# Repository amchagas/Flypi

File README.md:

#### Flypi - An open source, modular, affordable tool for imaging experiments.

Hi! Thanks for dropping by. This project started during one of the summer courses organized by [Trend in Africa](www.trendinafrica.org). It developed to the current state due to the efforts of many people along the way. In special Tom Baden, Lucia Prieto, and Edwin Cruz. A paper describing the system was published in [Plos Biology](http://journals.plos.org/plosbiology/article?id=10.1371/journal.pbio.2002702).

 Version 1.0 was released with the paper and can be found [here](https://github.com/amchagas/Flypi/tree/v1.0.0).

The system can be used for optical microscopy, fluorescence, behavioural tracking, optogenetics, calcium imaging and thermogenetics (see examples recorded with the system below).

#### Some samples imaged with the device:

|     |   |    |
|---|---|---|
|    |   |    |

### Custom PCB

You can order the PCBs and buy the parts to assemble them through the [Kitspace page](https://kitspace.org/boards/github.com/prometheus-science/FlyPi).

#### Necessary Libraries:

LED Ring from Adafruit:
https://github.com/adafruit/Adafruit_NeoPixel

LED Matrix from Adafruit:
https://github.com/adafruit/Adafruit-LED-Backpack-Library

gpac library:
sudo apt-get update
sudo apt-get install gpac

## *.h264 conversion to *.avi:
Done via gpac. MP4BOX.

## Zipped SD Card image containing Raspian image with all things installed:

[IMAGE](https://bit.ly/flyipimg)

## Contributors ✨

Thanks goes to these wonderful people ([emoji key](https://allcontributors.org/docs/en/emoji-key)):

<!-- ALL-CONTRIBUTORS-LIST:START - Do not remove or modify this section -->
<!-- prettier-ignore -->
<table>
  <tr>
    <td align="center"><a href="http://www.openeuroscience.com"><br /><sub><b>Andre Maia Chagas</b></sub></a><br /><a href="https://github.com/amchagas/Flypi/commits?author=amchagas" title="Code">💻</a> <a href="#design-amchagas" title="Design">🎨</a> <a href="https://github.com/amchagas/Flypi/commits?author=amchagas" title="Documentation">📖</a></td><td align="center"><a href="https://github.com/icaven"><br /><sub><b>icaven</b></sub></a><br /><a href="#design-icaven" title="Design">🎨</a></td>
    <td align="center"><a href="https://github.com/GrandeCappuccino"><br /><sub><b>Edwin Cruz</b></sub></a><br /><a href="#design-GrandeCappuccino" title="Design">🎨</a></td><td align="center"><a href="http://www.badenlab.org"><br /><sub><b>Tom Baden</b></sub></a><br /><a href="#design-TomBaden" title="Design">🎨</a> <a href="https://github.com/amchagas/Flypi/commits?author=TomBaden" title="Code">💻</a></td><td align="center"><a href="https://github.com/isobianin"><br /><sub><b>Ihor Sobianin</b></sub></a><br /><a href="#design-isobianin" title="Design">🎨</a></td>
    <td align="center"><a href="https://kitspace.org"><br /><sub><b>Kaspar Emanuel</b></sub></a><br /><a href="https://github.com/amchagas/Flypi/commits?author=kasbah" title="Code">💻</a></td><td align="center"><a href="https://github.com/ifriad"><br /><sub><b>ifriad</b></sub></a><br /><a href="#design-ifriad" title="Design">🎨</a> <a href="https://github.com/amchagas/Flypi/commits?author=ifriad" title="Code">💻</a></td>
  </tr>
</table>

<!-- ALL-CONTRIBUTORS-LIST:END -->

This project follows the [all-contributors](https://github.com/all-contributors/all-contributors) specification. Contributions of any kind welcome!

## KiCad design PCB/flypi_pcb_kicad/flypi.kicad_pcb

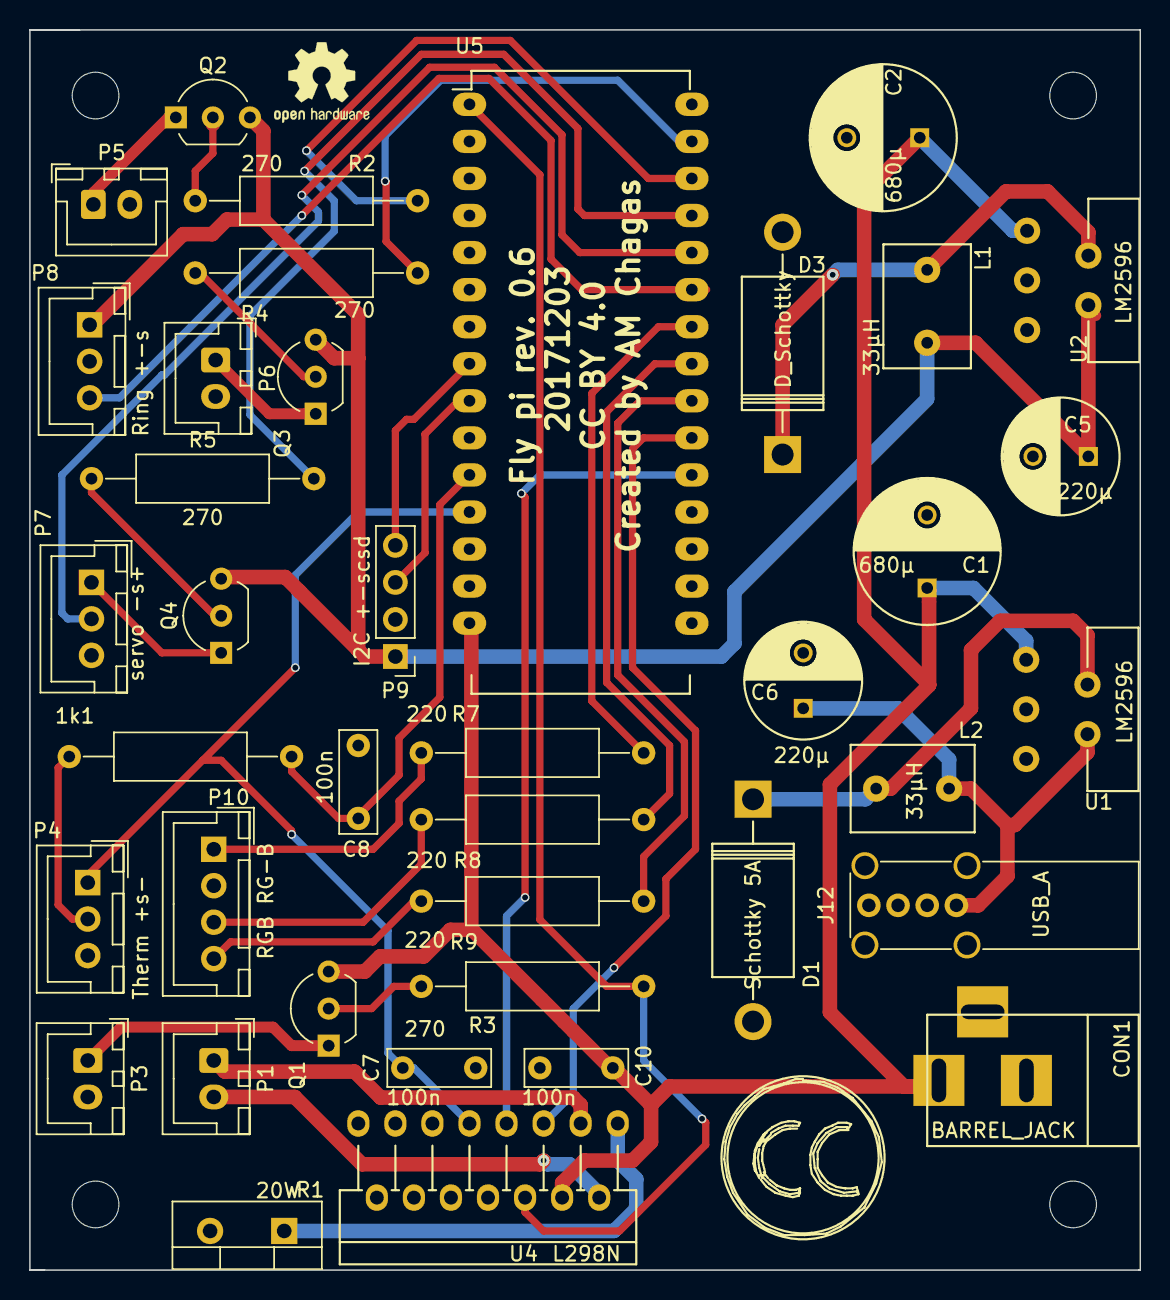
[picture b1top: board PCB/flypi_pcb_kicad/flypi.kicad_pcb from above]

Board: 2 copper layers, 76.1 x 85.0 mm, 40 parts (0 on the bottom side), 36 nets.

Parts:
1k1: R; R_Axial_DIN0309_L9.0mm_D3.2mm_P15.24mm_Horizontal
 : MountingHole_3.2mm_M3_DIN965
C1, C2: 680µ; C_Radial_D10_L21_P5
C5, C6: 220µ; C_Radial_D8_L13_P3.8
C7, C8, C10: 100n; C_Rect_L7.0mm_W2.5mm_P5.00mm
CON1: BARREL_JACK
D1: Schottky 5A; Diode_DO-201AD_Horizontal_RM15
D3: D_Schottky; Diode_DO-201AD_Horizontal_RM15
J12: USB_A; USB_A_Vertical
L1, L2: 33µH; Neosid_Inductor_MA-Bs75
P1: PeltS1S2; JST_XH_B2B-XH-A_1x02_P2.50mm_Vertical
P3: Fan+-; JST_XH_B2B-XH-A_1x02_P2.50mm_Vertical
P4: Therm +s-; JST_XH_B03B-XH-A_03x2.50mm_Straight
P5: HP1+-; JST_XH_B2B-XH-A_1x02_P2.50mm_Vertical
P6: HP2+-; JST_XH_B2B-XH-A_1x02_P2.50mm_Vertical
P7: servo -s+; JST_XH_B03B-XH-A_03x2.50mm_Straight
P8: Ring +-s; JST_XH_B03B-XH-A_03x2.50mm_Straight
P9: I2C +-scsd; Socket_Strip_Straight_1x04_Pitch2.54mm
P10: RGB RG-B; JST_XH_B04B-XH-A_04x2.50mm_Straight
Q1, Q3, Q4: 1A_NPN_EBC; TO-92_Inline_Wide
Q2: 1A-NPN-EBC; TO-92_Inline_Wide
R1: 20W; TO-220-2_Vertical
R2, R3, R4, R5: 270; R_Axial_DIN0309_L9.0mm_D3.2mm_P15.24mm_Horizontal
R7, R8, R9: 220; R_Axial_DIN0309_L9.0mm_D3.2mm_P15.24mm_Horizontal
U1, U2: LM2596
U4: L298N; Multiwatt_15_Vertical
U5: arduino_mini; DIP-30_W15.24mm_LongPads

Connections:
GND: C1.2, C2.2, C5.2, C6.2, C7.2, C8.1, C10.1, CON1.2, CON1.3, D1.2, D3.2, J12.4, J12.5, P3.2, P4.3, P5.2, P6.2, P7.3, P8.2, P9.2, P10.2, R1.2, U1.3, U1.5, U2.3, U2.5, U4.8, U5.14, U5.19
unnamed: 1k1.1, C8.2, U5.11
unnamed: 1k1.2, P4.2
unnamed: C1.1, C2.1, C10.2, CON1.1, Q1.3, U1.1, U2.1, U4.4, U5.15
unnamed: C5.1, L1.2, P8.1, P9.1, Q2.3, Q3.3, Q4.3, U2.4
unnamed: C6.1, J12.1, L2.2, U1.4
unnamed: C7.1, P4.1, U4.9, U5.12
unnamed: D1.1, L2.1, U1.2
unnamed: D3.1, L1.1, U2.2
unnamed: P1.1, U4.3
unnamed: P1.2, U4.2
unnamed: P3.1, Q1.1
unnamed: P5.1, Q2.1
unnamed: P6.1, Q3.1
unnamed: P7.1, Q4.1
unnamed: P7.2, U5.26
unnamed: P8.3, U5.25
unnamed: P9.3, U5.9
unnamed: P9.4, U5.8
unnamed: P10.1, R7.1
unnamed: P10.3, R8.1
unnamed: P10.4, R9.1
unnamed: Q1.2, R3.1
unnamed: Q2.2, R2.1
unnamed: Q3.2, R4.1
unnamed: Q4.2, R5.1
unnamed: R1.1, U4.1
unnamed: R2.2, U5.28
unnamed: R3.2, U4.6, U5.1
unnamed: R4.2, U5.29
unnamed: R5.2, U5.27
unnamed: R7.2, U5.24
unnamed: R8.2, U5.23
unnamed: R9.2, U5.22
unnamed: U4.5, U5.21
unnamed: U4.7, U5.20

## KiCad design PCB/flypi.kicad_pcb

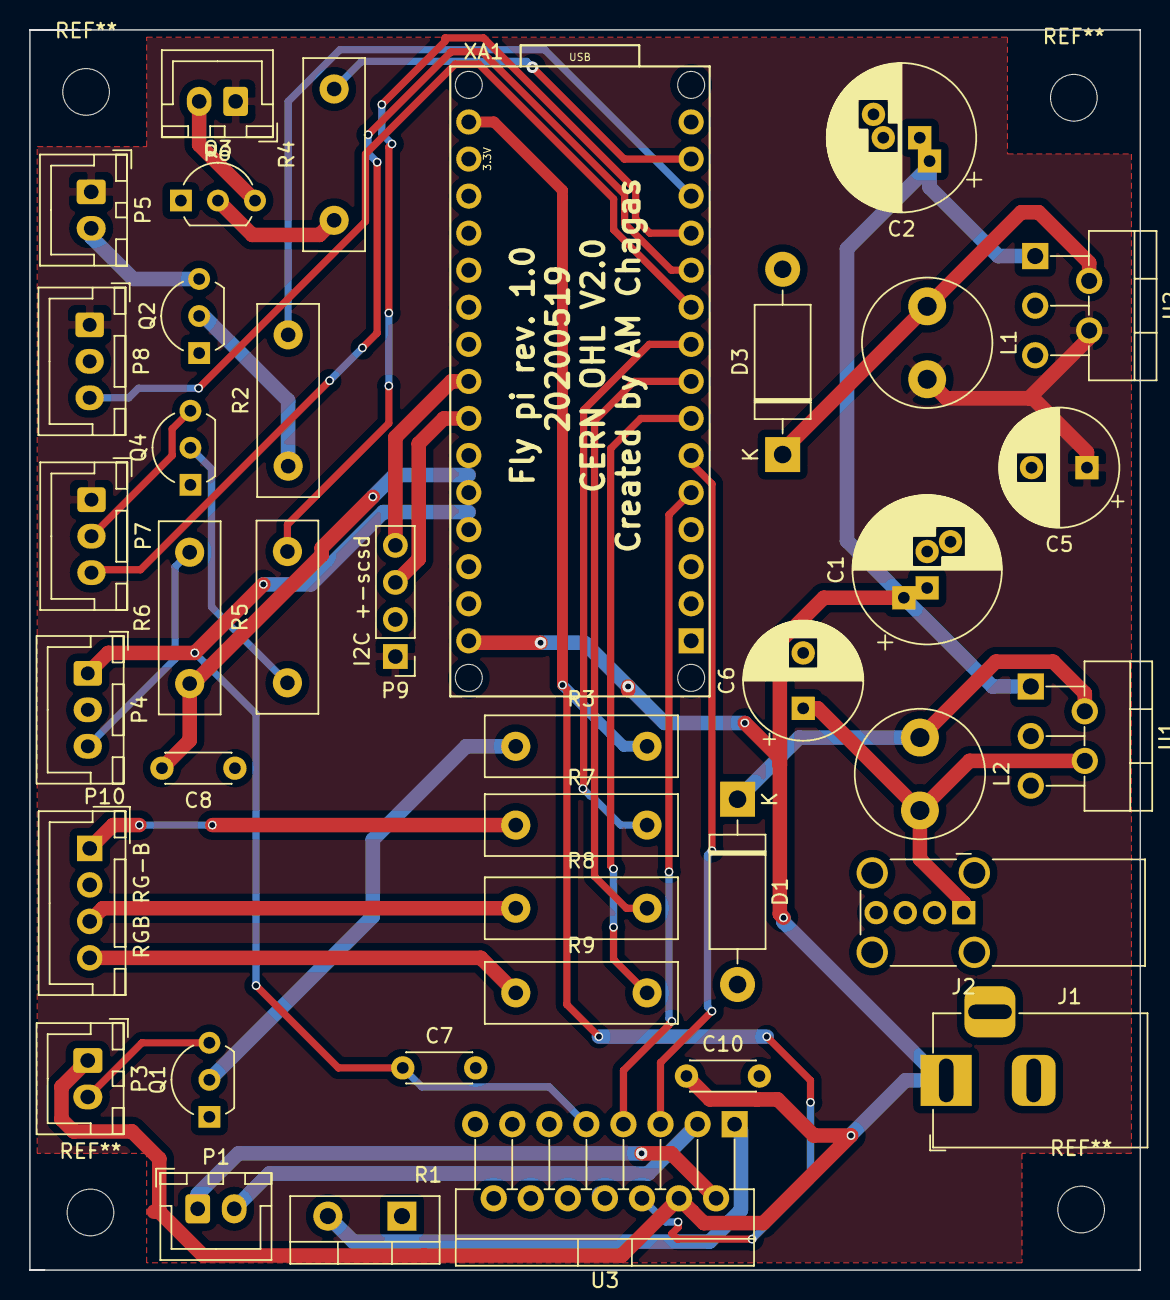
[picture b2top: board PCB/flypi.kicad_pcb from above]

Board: 2 copper layers, 76.1 x 85.0 mm, 39 parts (0 on the bottom side), 36 nets.

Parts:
C1, C2: 680µ; CP_Radial_D10.0mm_P2.50mm_P5.00mm
C5, C6: 220µ; CP_Radial_D8.0mm_P3.80mm
C7, C8, C10: 100n; C_Disc_D4.3mm_W1.9mm_P5.00mm
D1: Schottky 5A; D_DO-15_P12.70mm_Horizontal
D3: Schottky_5A; D_DO-15_P12.70mm_Horizontal
J1: Barrel_Jack_MountingPin; BarrelJack_Horizontal
J2: USB_A; USB_A_Wuerth_614004134726_Horizontal
L1, L2: 33µH; L_Radial_D8.7mm_P5.00mm_Fastron_07HCP
P1: PeltS1S2; JST_XH_B2B-XH-A_1x02_P2.50mm_Vertical
P3: Fan+-; JST_XH_B2B-XH-A_1x02_P2.50mm_Vertical
P4: Therm +-S; JST_XH_B3B-XH-A_1x03_P2.50mm_Vertical
P5: HP1+-; JST_XH_B2B-XH-A_1x02_P2.50mm_Vertical
P6: HP2+-; JST_XH_B2B-XH-A_1x02_P2.50mm_Vertical
P7: servo +-S; JST_XH_B3B-XH-A_1x03_P2.50mm_Vertical
P8: Ring +-s; JST_XH_B3B-XH-A_1x03_P2.50mm_Vertical
P9: I2C +-scsd; Socket_Strip_Straight_1x04_Pitch2.54mm
P10: RGB RG-B; JST_XH_B04B-XH-A_04x2.50mm_Straight
Q1, Q3, Q4: 1A_NPN_EBC; TO-92L_Inline_Wide
Q2: 1A-NPN-EBC; TO-92L_Inline_Wide
R1: 20W; TO-220-2_Vertical
R2, R3, R4, R5, R7, R8, R9: 270; R_Box_L13.0mm_W4.0mm_P9.00mm
R6: 1k1; R_Box_L13.0mm_W4.0mm_P9.00mm
U1, U2: LM2596S-5; TO-220-5_P3.4x3.7mm_StaggerOdd_Lead3.8mm_Vertical
U3: L298HN; TO-220-15_P2.54x2.54mm_StaggerOdd_Lead4.58mm_Vertical
XA1: Arduino_Nano_Socket

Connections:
+5V: C5.1, L1.2, P5.1, P6.1, P7.1, P8.1, P9.1, U2.4
+5VD: C7.1, P4.1, U3.9, XA1.5V
+12V: C1.1, C2.1, C10.1, J1.1, P3.1, U1.1, U2.1, U3.4, XA1.VIN
Fan: R3.2, U3.6, XA1.D13
GND: C1.2, C2.2, C5.2, C6.2, C7.2, C8.1, C10.2, D1.2, D3.2, J1.2, J2.4, J2.5, P4.2, P8.2, P9.2, P10.2, Q1.1, Q2.1, Q3.1, Q4.1, R1.1, U1.3, U1.5, U2.3, U2.5, U3.8, XA1.GND1, XA1.GND2
HP1: R2.2, XA1.D10
HP2: R4.2, XA1.D11
unnamed: C6.1, J2.1, L2.2, U1.4
unnamed: D1.1, L2.1, U1.2
unnamed: D3.1, L1.1, U2.2
unnamed: P1.1, U3.2
unnamed: P1.2, U3.3
unnamed: P3.2, Q1.3
unnamed: P4.3, R6.2
unnamed: P5.2, Q2.3
unnamed: P6.2, Q3.3
unnamed: P7.2, Q4.3
unnamed: P10.1, R7.1
unnamed: P10.3, R8.1
unnamed: P10.4, R9.1
unnamed: Q1.2, R3.1
unnamed: Q2.2, R2.1
unnamed: Q3.2, R4.1
unnamed: Q4.2, R5.1
unnamed: R1.2, U3.1
Peltier_input1: U3.5, XA1.D3
Peltier_input2: U3.7, XA1.D2
RGBlue: R7.2, XA1.D6
RGreenB: R8.2, XA1.D5
RedGB: R9.2, XA1.D4
Ring: P8.3, XA1.D7
SCL: P9.3, XA1.A5
SDA: P9.4, XA1.A4
servo_signal: P7.3, XA1.D8
servo_switch: R5.2, XA1.D9
temp_sensor: C8.2, R6.1, XA1.A7

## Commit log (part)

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2017-06-18 Fix README titles
2017-07-18 updated user manual
2017-07-27 created bill of materials with ali express suppliers
2017-10-06 bumped up serial and disabled mock up
2017-10-18 Correct the gear teeth shape, round mount corners, correct the excitation tube openings
2017-11-03 update bill of materials
2017-11-03 no change to 3D scad
2017-11-03 individual parts added as stls
2017-11-03 added stl plates containing organized parts
2017-11-03 Support two different viewing modes, exploded view, and printable layout, and allow printing of batches of parts
2017-11-03 Update the sliding tolerance to track changes in the main branch
2017-11-03 Specify which version of the FlyPi scad files the README refers to
2017-11-05 update 3d print files, and start the idea of having a library for common structures in the pieces
2017-11-06 change to gerber files
2017-11-15 add file containing old autofocus code by ihab, to solve bug reported by Tom
2017-11-16 resolved weird issues with serial and kept changes in pcb, 3d files and etc
2017-11-16 Change for placement of parts into batches for printing (#20)
    * repo clean uo, moving old and unused files to specific folders
    * removing old files
    * add new bill of materials
    * update camholder for picamera v2
    * Fix README titles
    * Update README.md
2017-11-16 renamed Icaven's file to flypi_v30.scad
2017-12-30 Update fly_pi_development.ino
    remove matrix controls.
2017-12-30 Update fly_pi_development.ino
    remove matrix commands
2018-01-02 major revision to python code. Reduced the number of recursive functions and data transmitted to arduino are now done only via flypiapp.py. Seems to have fixed protocols bugs and speeded up the Pelti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
2018-01-02 cleaned up arduino code. Changed answer token and removed code related to matrix and unused ring functions
2018-01-02 created individual files for each part to be 3D printed. Should make life easier for creating new parts and placing parts to be printed in batches. As well as rounding edges
2018-01-02 3D print files cleanup
2018-02-02 updated pcb, so that screw holes are equidistant from board edges
2018-02-05 some clean up to 3d print files
2018-02-05 rename assembly manual to match publication and link
2018-03-06 update arduino code for ring with 4 leds per bit
2018-03-07 Start a kitspace BOM for the SMD version
2018-03-08 update gerber1 folder to gerber
2018-03-08 Update kitspace.yaml
    changed the folder where kitspace will look for pcb and gerber
2018-03-08 update gebers
2018-03-09 found bug in gerbers
2018-03-09 Prepare for kitspace (#22)
    * update to pcbs. Both SMD and new through hole. PCB is untested.
    * update 3d print files, and start the idea of having a library for common structures in the pieces
    * change to gerber files
    * update to pcb labels (corrected inverted values)
    * removed matrix commands from Arduino
    * major revision to python code. Reduced the number of recursive functions and data transmitted to arduino are now done only via flypiapp.py. Seems to have fixed protocols bugs and speeded up the Pel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
2018-03-09 Revert "Prepare for kitspace (#22)" (#23)
    This reverts commit 9aa00d109e1364754c2a30ef1fc76aca93cc7955.
2018-03-09 revert last commit
2018-03-09 Make 1-click-bom as complete as possible
2018-03-09 Re-plot gerbers without sheet references
2018-03-09 Add summary and hackaday.io link to kitspace.yaml
2018-03-09 Clean up README and add link to Kitspace page
2018-03-09 Fix some issues with BOM
2018-03-09 Improve 1-click-bom some more
2018-03-10 updated with components not in pcb
2018-03-10 more updates
2018-03-10 1click bom update
2018-03-10 added UV led
2018-03-16 added some components, fixed some wrong parts
2018-04-06 update components of one click BOM
2018-04-06 uploaded new printed parts and rearranged the folder structure for 3d models
2018-06-05 Rename 1-click-bom.tsv.txt to 1-click-bom.tsv
2018-06-21 update_bom
2018-07-16 clean_up STLs
2018-07-26 renamed stls
2018-08-13 update one click bon
2018-08-16 fix stls
2018-08-16 update 3d files
2018-08-16 update manipulator and manual
2018-08-16 bring all updates from Prometheus development to original repo (#25) (#26)
    * bring all updates from Prometheus development to original repo (#25)
    * small corrections to the timing address for LEDs
    * first change on the protocol class
    * added schematics for electronics, python code and overall components
    * updated gerber files
    * updated BOM
2018-08-17 more clean up
2018-08-17 clean up of bill of materials
2018-08-17 out of use files related to the pcb
2018-08-17 out of use files for the boms
2018-08-17 clean kitspace.yaml
2018-08-17 clean readme.md
2018-08-17 clean up scad file for version 1.0
2018-08-17 clean up arduino code
2018-08-17 update PCB and gerber
2018-08-17 more cleanup of 3d files structure
2018-08-17 clean up arduino code and add RGBW ring option
2018-08-17 update BOM pointer
2018-08-17 update bom
2018-08-17 update bom3
2018-08-17 bom4
2018-08-19 update 1-click bom
2018-08-26 rename one of the arduino sketch folders
2018-08-26 remove missnamed folder
2018-09-14 update camera.py. AVI conversion improved by forum user mattj1061
2018-09-14 updated code to save peltier readings to file. now data is properly organized as two columns. One of time and one for temperature
2018-09-14 remove files with .STL extension
2018-09-14 add stl plates for easy printing
2018-09-14 remove gcode plates for now
2018-09-14 updated some separators to semi-colon
2018-09-14 first steps added folder with images and gifs
2018-09-26 more updates and tests
2018-09-26 Readme overhaul (#32)
    * first steps added folder with images and gifs
    * more updates and tests
    * more updates to readme
    * update readme
    * update readme
2018-09-28 incorporate changes made elsewhere
2018-09-28 revert to 98f9291
2018-10-01 Update flypiapp to load without arduino connected
2018-10-02 clean up development.ino
2018-10-25 move all media from readme to remote repo, so that downloading the repo doesn't take so long
2018-10-25 remove media folder
2018-10-25 remove unnecessary files
2018-11-10 correct csv rendering
2018-12-06 first tests with new serial protocol
2018-12-06 update of GUI using qt
2018-12-07 update serial
2019-01-01 updated ring controls, led controls and camera controls
2019-01-02 update to leds and ring controls
2019-01-02 update leds ring
2019-01-02 update led arduino cmmand
2019-01-21 update to new serial communication and modularization of arduino code
2019-01-22 move ring funcs to its own header file
2019-01-22 cleanup serial sketch on arduino and further development on protocols qt
2019-01-27 added gitignore pyc and what nots
2019-01-27 update to serial and protocols_qt
2019-01-27 update to camera class and protocols
2019-02-04 started adding time lapse, recording, file conversion to gui
2019-03-04 update camera class
2019-03-13 finished implementation of protocol peltier
2019-05-12 changes to arduino code
2019-05-12 changes to python code
2019-05-16 update serial test suite
2019-05-16 remove qt implementation from master
2019-05-26 add individual files for manipulator
2019-05-27 added light diffuser step
2019-06-12 update arduino code on serial test
2019-07-01 renaming files of the user interface and bringing in new version (where there are only two main files, one describing the GUI and one describing the callbacks)
2019-07-02 update new arduino serial system. Servo, matrix and peltier implementation
2019-08-01 updates to serialupdate
2019-08-01 work on peltier class, graphing data, and logging it to file
2019-08-03 added leds to protocol
2019-08-03 added comment with idea to make peltier more precise during protocol
2019-08-04 removed some comments and fixed binning callbaclk
2019-08-04 implement h264 to avi conversion
2019-08-04 clean repo
2019-08-05 new link to zipped image
2019-08-09 testing downloads badge
2019-08-09 test download badge
2019-08-09 more testing
2019-08-09 grrr
2019-08-09 final mess around
2019-08-13 increased the max time allowed in protocols
2019-08-18 Create sobianin
2019-08-18 Version with hinges and improved closing system
2019-08-18 Lightweight version
2019-08-26 fix bug in protocol when no recording is being made
2019-08-26 make recording videos on protocol more flexible.
2019-08-26 fix led classes
2019-08-28 Updated tolerances
2019-09-02 fix bug on led1 slider
2019-09-10 Create Manipulator_Zaxis_T_holding_system
2019-09-10 Shaft dimensions to use in designs
2019-10-04 rearranged and renamed step files so that they follow an extension convention
2019-10-06 added okh.yml file to flypi repo
2019-10-15 Make okh-flypi.yml valid yaml
    - There is an issue with OKH 1.0 so I removed the version at the top: https://app.standardsrepo.com/MakerNetAlliance/OpenKnowHow/issues/263
    - There were some indentation issues
2019-10-15 Make okh-flypi.yml valid yaml (#56)
    - There is an issue with OKH 1.0 so I removed the version at the top: https://app.standardsrepo.com/MakerNetAlliance/OpenKnowHow/issues/263
    - There were some indentation issues
2019-10-15 Fix use of @ in okh-flypi.yml (#57)
    Forgot one
2019-10-23 Updated LED holder (#55)
    * Create sobianin
    * Delete sobianin
    * Create Manipulator_Zaxis_v2.STEP
    * Add files via upload
    * Rename RaspberryCase_Top.stp to RaspberryCase_Top_v2.stp
    * Version with hinges and improved closing system
2019-10-29 update code to open serial port and arduino comm
2019-10-29 Serialupdate (#58)
    * first qt5 implementation
    * first tests with new serial protocol
    * update of GUI using qt
    * update serial
    * more updates
    * added green, blue channels to ring and peltier callbacks
2019-11-03 update python code to kill bug when using leds and protocol
2019-11-11 removed out of place text in code
2019-11-11 fixed bug that didn't allow for long protocol rungs
2019-11-16 testing travis setup
2019-11-16 start building requirements
2019-11-16 install with pip3
2019-11-16 install with pip
2019-11-16 adsd libraries
2019-11-16 change approach. simulate arm on travis
2019-11-16 removing CI from repository
2019-11-17 docs: update README.md
2019-11-17 docs: create .all-contributorsrc
2019-11-17 docs: update .all-contributorsrc
2019-11-17 docs: add kasbah as a contributor (#65)
    * docs: update README.md
    * docs: update .all-contributorsrc
2019-11-17 Update .all-contributorsrc
2019-11-17 docs: add ifriad as a contributor (#66)
    * docs: update README.md
    * docs: update .all-contributorsrc
2019-11-17 docs: add GrandeCappuccino as a contributor (#68)
    * docs: update README.md
    * docs: update .all-contributorsrc
    * docs: update README.md
    * docs: update .all-contributorsrc
2019-11-17 docs: add icaven as a contributor (#69)
    * docs: update README.md
    * docs: update .all-contributorsrc
    * docs: update README.md
    * docs: update .all-contributorsrc
2020-05-18 first implementation of the board being ported to KiCad5 and proper wiring of transistors
2020-06-09 finished improving schematics and updated the board itself
2020-08-08 update 1-click-bom
2020-11-19 update link to SD card image
2020-11-26 Server-client type connection for PiCamera
2020-12-04 clean up 3Dprint files and start porting PCB to kicad5
2020-12-09 Updated GUI
2020-12-10 Upload files
    Added all the necessary files with folder structure akin to the master
2020-12-10 Restucture repository
2020-12-30 Addition of camera streaming and minor GUI enhancements (#71)
    * Create sobianin
    * Delete sobianin
    * Create Manipulator_Zaxis_v2.STEP
    * Add files via upload
    * Rename RaspberryCase_Top.stp to RaspberryCase_Top_v2.stp
    * Version with hinges and improved closing system
2020-12-30 repository clean up
2021-05-06 remove obsolete part from BOM and update it
2021-05-06 remove locj file
2021-05-12 fix misslabeling on board
2021-05-12 more silly testing
2021-05-12 more silly testing and remove forum information
2022-02-14 Various OKH fixes
    * YAML syntax fixes
    * move description form title to description
    * prefer repo-local path over URL to in-repo files
    * use SPDX compliant license identifiers
2022-02-15 Various OKH fixes (#77)
    * YAML syntax fixes
    * move description form title to description
    * prefer repo-local path over URL to in-repo files
    * use SPDX compliant license identifiers

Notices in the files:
PCB/flypi.kicad_pcb:
CERN OHL V2.0
PCB/flypi_pcb_kicad/flypi.kicad_pcb:
CC BY 4.0
